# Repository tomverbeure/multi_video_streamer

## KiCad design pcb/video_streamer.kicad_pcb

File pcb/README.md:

# Multi-Video Streamer

Nothing to see here yet...

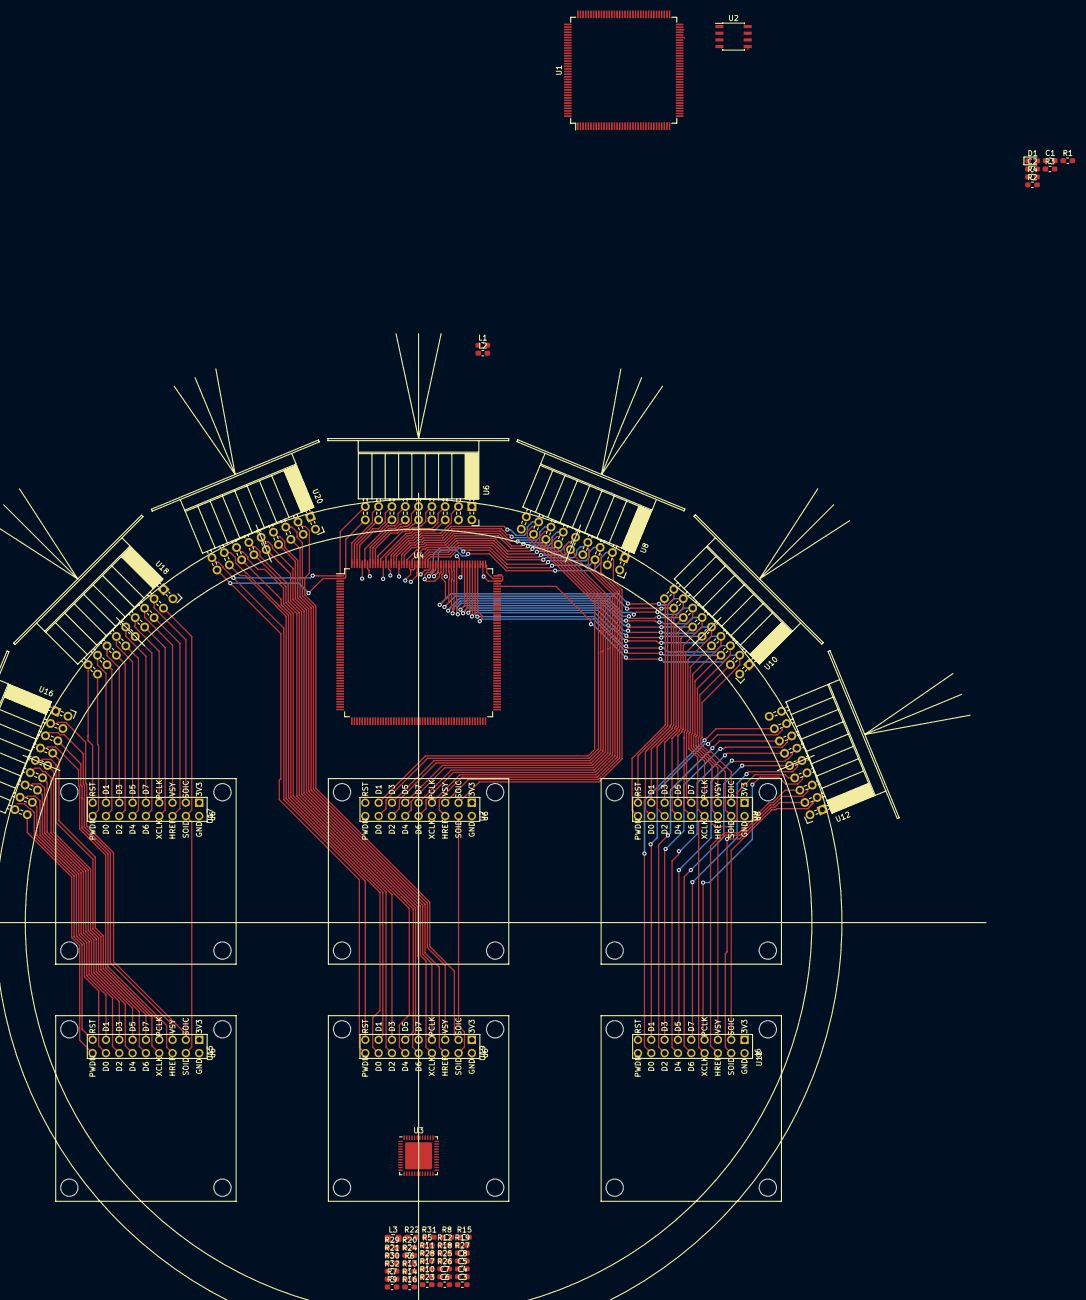
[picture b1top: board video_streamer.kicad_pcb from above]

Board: 2 copper layers, 61 parts (0 on the bottom side), 120 nets.

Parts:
C1, C2: C; C_0603_1608Metric_Pad1.05x0.95mm_HandSolder
C3, C4, C5, C6: 0.1uF; C_0603_1608Metric_Pad1.05x0.95mm_HandSolder
C7, C8: 27pF; C_0603_1608Metric_Pad1.05x0.95mm_HandSolder
D1: BAS70J; D_0603_1608Metric_Pad1.05x0.95mm_HandSolder
L1, L2: 600R; L_0603_1608Metric_Pad1.05x0.95mm_HandSolder
L3: L; L_0805_2012Metric_Pad1.15x1.40mm_HandSolder
R1, R2, R3, R5, R7, R9, R11, R13, R15, R17, R18, R19, R32: 10K; R_0603_1608Metric_Pad1.05x0.95mm_HandSolder
R4, R6, R8, R10, R12, R14, R16: NS; R_0603_1608Metric_Pad1.05x0.95mm_HandSolder
R20, R21, R25: 1K; R_0603_1608Metric_Pad1.05x0.95mm_HandSolder
R22, R23: 0; R_0603_1608Metric_Pad1.05x0.95mm_HandSolder
R24: 12.1K 1%; R_0603_1608Metric_Pad1.05x0.95mm_HandSolder
R26, R27, R28, R29, R30, R31: 22; R_0603_1608Metric_Pad1.05x0.95mm_HandSolder
U1: ICE40HX4K-144; TQFP-144_20x20mm_P0.5mm
U2: AT25SF041-SSHD; SOIC-8_3.9x4.9mm_P1.27mm
U3: KSZ9031RNXCA; QFN-48-1EP_7x7mm_P0.5mm_EP5.15x5.15mm
U4: EP2C8Q208; PQFP-208_28x28mm_P0.5mm
U6, U8, U10, U12, U16, U18, U20: OV7670_module; OV7670_Vertical
U7, U9, U11, U15, U17, U19: OV7670_module; OV7670_Flat

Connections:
+1V2: L1.1, L2.1, U3.14, U3.18, U3.23, U3.26, U3.30, U3.39, U4.32, U4.51, U4.53, U4.66, U4.79, U4.120, U4.155, U4.157, U4.178, U4.190
+3.3VA: C1.1, C2.2, U1.54, U1.126
+3V3: D1.2, L3.1, R1.2, R2.2, R3.2, R5.1, R7.1, R9.1, R11.1, R13.1, R15.1, R20.1, R21.1, R25.1, R32.1, U1.6, U1.27, U1.30, U1.40, U1.46, U1.57, U1.72, U1.89, U1.92, U1.100, U1.111, U1.123, U1.131, U2.8, U3.16, U3.34, U3.40, U4.7, U4.14, U4.29, U4.42, U4.62, U4.71, U4.83, U4.91, U4.98, U4.109, U4.122, U4.136, U4.148, U4.166, U4.172, U4.183, U4.194, U4.202, U6.1, U7.1, U8.1, U9.1, U10.1, U11.1, U12.1, U15.1, U16.1, U17.1, U18.1, U19.1, U20.1
/EP2C8/ov0_d0: U4.207, U6.16
/EP2C8/ov0_d1: U4.208, U6.15
/EP2C8/ov0_d2: U4.205, U6.14
/EP2C8/ov0_d3: U4.206, U6.13
/EP2C8/ov0_d4: U4.201, U6.12
/EP2C8/ov0_d5: U4.203, U6.11
/EP2C8/ov0_d6: U4.199, U6.10
/EP2C8/ov0_d7: U4.200, U6.9
/EP2C8/ov1_d0: U4.191, U7.16, U8.16
/EP2C8/ov1_d1: U4.192, U7.15, U8.15
/EP2C8/ov1_d2: U4.188, U7.14, U8.14
/EP2C8/ov1_d3: U4.189, U7.13, U8.13
/EP2C8/ov1_d4: U4.185, U7.12, U8.12
/EP2C8/ov1_d5: U4.187, U7.11, U8.11
/EP2C8/ov1_d6: U4.181, U7.10, U8.10
/EP2C8/ov1_d7: U4.182, U7.9, U8.9
/EP2C8/ov2_d0: U4.171, U9.16, U10.16
/EP2C8/ov2_d1: U4.173, U9.15, U10.15
/EP2C8/ov2_d2: U4.169, U9.14, U10.14
/EP2C8/ov2_d3: U4.170, U9.13, U10.13
/EP2C8/ov2_d4: U4.165, U9.12, U10.12
/EP2C8/ov2_d5: U4.168, U9.11, U10.11
/EP2C8/ov2_d6: U4.163, U9.10, U10.10
/EP2C8/ov2_d7: U4.164, U9.9, U10.9
/Ethernet/clk25: R22.1, U3.46
/Ethernet/clk125: R15.2, R16.2, U3.41
/Ethernet/eth_int_n: R32.2, U3.38
/Ethernet/eth_led1_n: R17.2, U3.17
/Ethernet/eth_led2_n: R18.2, U3.15
/Ethernet/eth_mdio: R25.2, U3.37
/Ethernet/eth_rx_clk: R19.2, R31.2, U3.35
/Ethernet/eth_rx_dv: R5.2, R6.2, R26.2, U3.33
/Ethernet/eth_rxd0: R7.2, R8.2, R27.2, U3.32
/Ethernet/eth_rxd1: R9.2, R10.2, R28.2, U3.31
/Ethernet/eth_rxd2: R11.2, R12.2, R29.2, U3.28
/Ethernet/eth_rxd3: R13.2, R14.2, R30.2, U3.27
/ICE40/spi_sck: U1.70, U2.6
/ICE40/spi_sdi: U1.68, U2.5
/ICE40/spi_sdo: U1.67, U2.2
/ICE40/spi_ss: R1.1, R4.2, U1.71, U2.1
/OV7670 Sensor 3/ov_d0: U11.16, U12.16
/OV7670 Sensor 3/ov_d1: U11.15, U12.15
/OV7670 Sensor 3/ov_d2: U11.14, U12.14
/OV7670 Sensor 3/ov_d3: U11.13, U12.13
/OV7670 Sensor 3/ov_d4: U11.12, U12.12
/OV7670 Sensor 3/ov_d5: U11.11, U12.11
/OV7670 Sensor 3/ov_d6: U11.10, U12.10
/OV7670 Sensor 3/ov_d7: U11.9, U12.9
/OV7670 Sensor 4/ov_d0: U15.16, U16.16
/OV7670 Sensor 4/ov_d1: U15.15, U16.15
/OV7670 Sensor 4/ov_d2: U15.14, U16.14
/OV7670 Sensor 4/ov_d3: U15.13, U16.13
/OV7670 Sensor 4/ov_d4: U15.12, U16.12
/OV7670 Sensor 4/ov_d5: U15.11, U16.11
/OV7670 Sensor 4/ov_d6: U15.10, U16.10
/OV7670 Sensor 4/ov_d7: U15.9, U16.9
/OV7670 Sensor 5/ov_d0: U17.16, U18.16
/OV7670 Sensor 5/ov_d1: U17.15, U18.15
/OV7670 Sensor 5/ov_d2: U17.14, U18.14
/OV7670 Sensor 5/ov_d3: U17.13, U18.13
/OV7670 Sensor 5/ov_d4: U17.12, U18.12
/OV7670 Sensor 5/ov_d5: U17.11, U18.11
/OV7670 Sensor 5/ov_d6: U17.10, U18.10
/OV7670 Sensor 5/ov_d7: U17.9, U18.9
/OV7670 Sensor 6/ov_d0: U19.16, U20.16
/OV7670 Sensor 6/ov_d1: U19.15, U20.15
/OV7670 Sensor 6/ov_d2: U19.14, U20.14
/OV7670 Sensor 6/ov_d3: U19.13, U20.13
/OV7670 Sensor 6/ov_d4: U19.12, U20.12
/OV7670 Sensor 6/ov_d5: U19.11, U20.11
/OV7670 Sensor 6/ov_d6: U19.10, U20.10
/OV7670 Sensor 6/ov_d7: U19.9, U20.9
/ov0_href: U4.195, U6.6
/ov0_pclk: U4.198, U6.7
/ov0_soic: U4.193, U6.3
/ov0_vsync: U4.197, U6.5
/ov1_href: U4.176, U7.6, U8.6
/ov1_pclk: U4.180, U7.7, U8.7
/ov1_soic: U4.175, U7.3, U8.3
/ov1_vsync: U4.179, U7.5, U8.5
/ov2_href: U4.160, U9.6, U10.6
/ov2_pclk: U4.162, U9.7, U10.7
/ov2_soic: U4.152, U9.3, U10.3
/ov2_vsync: U4.161, U9.5, U10.5
/ov3_href: U11.6, U12.6
/ov3_pclk: U11.7, U12.7
/ov3_soic: U11.3, U12.3
/ov3_vsync: U11.5, U12.5
/ov4_href: U15.6, U16.6
/ov4_pclk: U15.7, U16.7
/ov4_soic: U15.3, U16.3
/ov4_vsync: U15.5, U16.5
/ov5_href: U17.6, U18.6
/ov5_pclk: U17.7, U18.7
/ov5_soic: U17.3, U18.3
/ov5_vsync: U17.5, U18.5
/ov6_href: U19.6, U20.6
/ov6_pclk: U19.7, U20.7
/ov6_soic: U19.3, U20.3
/ov6_vsync: U19.5, U20.5
/ov_pwdn: U4.2, U6.18, U7.18, U8.18, U9.18, U10.18, U11.18, U12.18, U15.18, U16.18, U17.18, U18.18, U19.18, U20.18
/ov_reset: U4.1, U6.17, U7.17, U8.17, U9.17, U10.17, U11.17, U12.17, U15.17, U16.17, U17.17, U18.17, U19.17, U20.17
/ov_soid: U6.4, U7.4, U8.4, U9.4, U10.4, U11.4, U12.4, U15.4, U16.4, U17.4, U18.4, U19.4, U20.4
/ov_xclk: U4.47, U6.8, U7.8, U8.8, U9.8, U10.8, U11.8, U12.8, U15.8, U16.8, U17.8, U18.8, U19.8, U20.8
GNDD: C3.2, C4.2, C5.2, C6.2, C7.2, C8.2, R4.1, R6.1, R8.1, R10.1, R12.1, R14.1, R16.1, R17.1, R18.1, R19.1, R24.2, U1.5, U1.13, U1.14, U1.59, U1.69, U1.103, U1.132, U1.140, U2.4, U3.29, U3.49, U4.9, U4.25, U4.36, U4.38, U4.49, U4.50, U4.52, U4.54, U4.55, U4.65, U4.73, U4.78, U4.85, U4.93, U4.100, U4.111, U4.119, U4.124, U4.140, U4.153, U4.154, U4.156, U4.158, U4.159, U4.167, U4.174, U4.177, U4.184, U4.186, U4.196, U4.204, U6.2, U7.2, U8.2, U9.2, U10.2, U11.2, U12.2, U15.2, U16.2, U17.2, U18.2, U19.2, U20.2
unnamed: C1.2, U1.53
unnamed: C2.1, U1.127
unnamed: C7.1, R22.2
unnamed: C8.1, R23.2
unnamed: D1.1, U1.108
unnamed: L1.2, U3.44
unnamed: L2.2, U3.4, U3.9
unnamed: L3.2, U3.1, U3.12
unnamed: R2.1, U2.7
unnamed: R3.1, U2.3
unnamed: R23.1, U3.45
unnamed: R24.1, U3.48

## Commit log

2019-02-17 First version.
2019-02-17 README.
2019-02-17 Move into ./pcb directory
2019-02-17 Move README back to top.
2019-02-17 Really move README to top.
2019-02-17 Fix library links.
2019-02-17 Cleanup files.
2019-02-18 OV flat footprint
2019-02-18 Cameras angled 22.5.
2019-02-18 Remove one flat sensor site.
2019-03-03 Update for latest EP2C8 symbol change.
